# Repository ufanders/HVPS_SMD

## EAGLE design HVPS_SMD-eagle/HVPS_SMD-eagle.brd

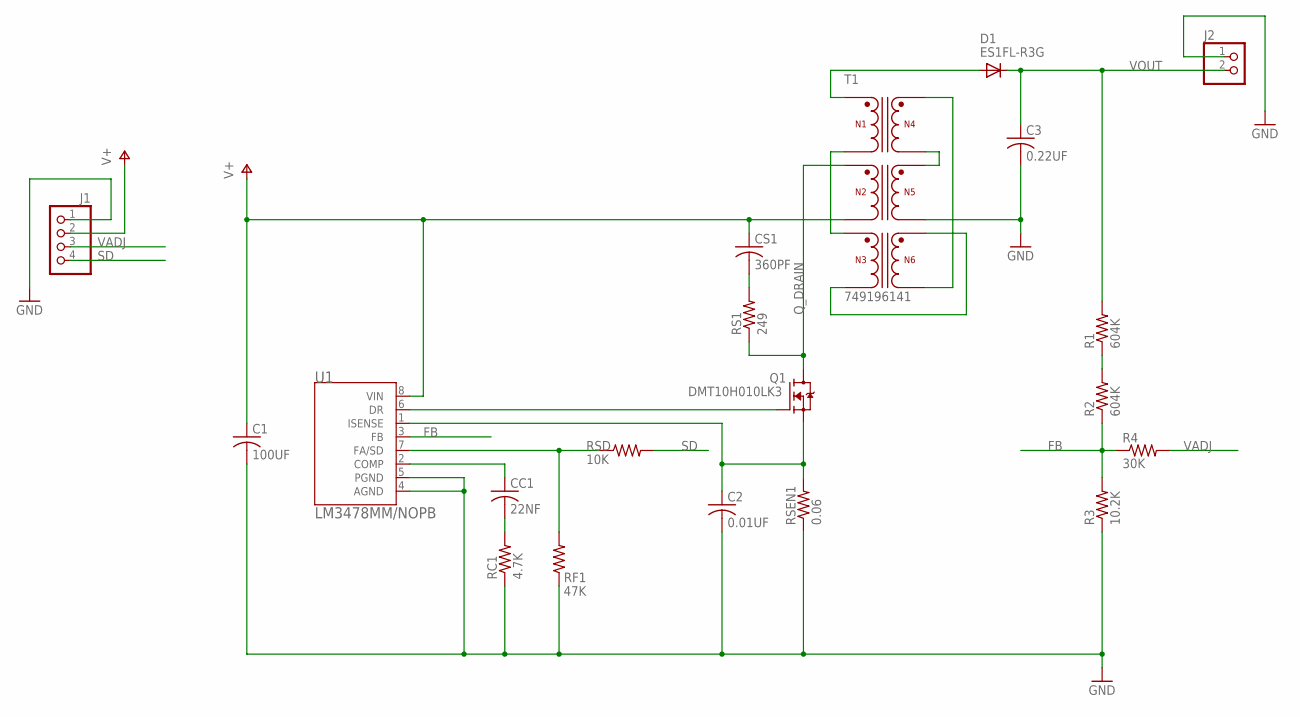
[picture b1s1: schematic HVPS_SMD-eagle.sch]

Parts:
C1: 100UF; C1210
C2: 0.01UF; C0603
C3: 0.22UF; C1210
CC1: 22NF; C0603
CS1: 360PF; C0603
D1: ES1FL-R3G; SMA
J1: PINHD-1X4; 1X04
J2: PINHD-1X2; 1X02
Q1: DMT10H010LK3; TO252
R1, R2: 604K; R0805
R3: 10.2K; R0603
R4: 30K; R0603
RC1: 4.7K; R0805
RF1: 47K; R0603
RS1: 249; R1206
RSD: 10K; R0603
RSEN1: 0.06; R2010
T1: 749196141
U1: LM3478MM/NOPB; MUA08A

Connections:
FB: R2.1, R3.2, R4.1, U1.3 (FB)
GND: C1.2, C2.2, C3.2, J1.1, J2.1, R3.1, RC1.1, RF1.1, RSEN1.1, T1.8 (N5), U1.4 (AGND), U1.5 (PGND)
unnamed: RF1.2, RSD.1, U1.7 (FA/SD)
unnamed: CC1.1, U1.2 (COMP)
unnamed: CC1.2, RC1.2
unnamed: C2.1, Q1.2 (S), RSEN1.2, U1.1 (ISENSE)
unnamed: T1.3 (N3), T1.4 (N1)
unnamed: T1.6 (N3), T1.12 (N6)
unnamed: CS1.2, RS1.2
unnamed: T1.9 (N6), T1.10 (N4)
unnamed: T1.7 (N4), T1.11 (N5)
unnamed: Q1.1 (G), U1.6 (DR)
unnamed: D1.A, T1.1 (N1)
unnamed: R1.1, R2.2
Q_DRAIN: Q1.3 (D), RS1.1, T1.2 (N2)
SD: J1.4, RSD.2
V+: C1.1, CS1.1, J1.2, T1.5 (N2), U1.8 (VIN)
VADJ: J1.3, R4.2
VOUT: C3.1, D1.C, J2.2, R1.2

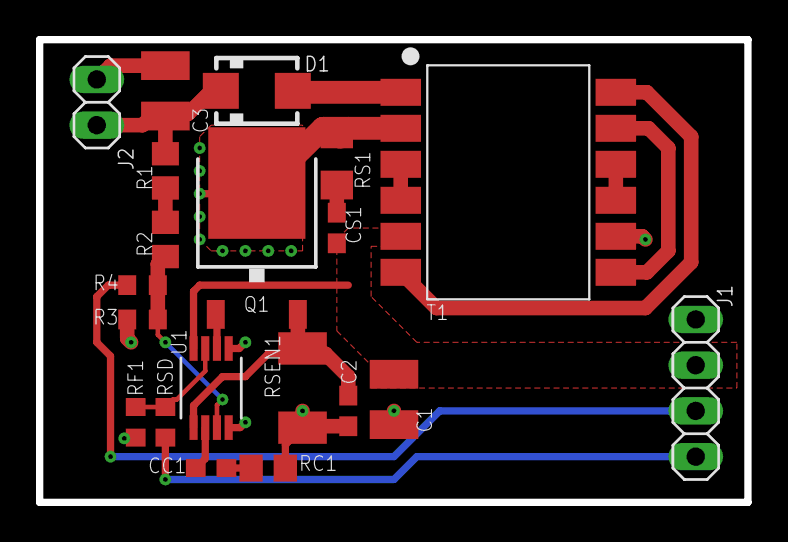
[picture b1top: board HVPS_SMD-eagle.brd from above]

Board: 2 copper layers, 39.4 x 25.7 mm, 20 parts (0 on the bottom side), 19 nets.

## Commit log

2018-12-23 -Schematic and layout created.
2018-12-23 -remove autosave.
2018-12-24 -gitignore.
2018-12-25 -Completed layout. -Added headers.
2019-01-10 -Reduced via drills. -Silkscreen cleanup. -Revision A.
2019-02-08 -EAGLE prefs file.
2019-02-08 -Updated design rules. -Added proper FA/SD signal path.
2019-05-11 -gitignore
